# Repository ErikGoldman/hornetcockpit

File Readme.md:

# Stuff to buy

* [Buttons](https://www.aliexpress.us/item/3256807596969239.html?spm=a2g0o.order_list.order_list_main.17.32181802tbzOcq&gatewayAdapt=glo2usa)
  * 3x for landing panel, 1x for emergency jet button

* [Rotary switches](https://www.aliexpress.us/item/3256806749667426.html?gps-id=pcStoreJustForYou&scm=1007.23125.137358.0&scm_id=1007.23125.137358.0&scm-url=1007.23125.137358.0&pvid=9bd218e7-9fd3-4785-a63d-b64e5d39fffa&_t=gps-id%3ApcStoreJustForYou%2Cscm-url%3A1007.23125.137358.0%2Cpvid%3A9bd218e7-9fd3-4785-a63d-b64e5d39fffa%2Ctpp_buckets%3A668%232846%238116%232002&pdp_npi=4%40dis%21USD%211.56%211.56%21%21%2111.33%2111.33%21%402103246617354162549406696e5c9c%2112000038783963415%21rec%21US%212054727994%21X&spm=a2g0o.store_pc_home.smartJustForYou_2004689678069.1005006935982178&gatewayAdapt=glo2usa)
  * 2 x 3-position for the DDI on/day/night
  * 1 x 5-position for jett select on the button box

* [Rtoary encoder](https://www.aliexpress.us/item/3256804721655912.html?spm=a2g0o.order_list.order_list_main.42.32181802tbzOcq&gatewayAdapt=glo2usa)
  * 2 for the UFC comm knobs

* [Switches](https://www.aliexpress.us/item/3256803381777279.html?spm=a2g0o.order_list.order_list_main.53.32181802tbzOcq&gatewayAdapt=glo2usa)
  * 4 x On-Off for the landing panel
  * 1 x On-Off-On for the landing panel (flaps switch)

* [Heavy on/off switch](https://www.aliexpress.us/item/3256807335530736.html?spm=a2g0o.order_list.order_list_main.72.32181802tbzOcq&gatewayAdapt=glo2usa)
  * 1  for Master Arm
  * 1 for landing gear on button box

* [Infinite metric inserts](https://www.aliexpress.us/item/3256806602613585.html?spm=a2g0o.order_list.order_list_main.78.32181802tbzOcq&gatewayAdapt=glo2usa)
  * You'll need M2, M3, and M4. Length doesn't matter that much.

* [Tactile switches](https://www.aliexpress.us/item/3256806726559452.html?spm=a2g0o.order_list.order_list_main.93.32181802tbzOcq&gatewayAdapt=glo2usa)
  * You'll need ~25 B3F-1025 buttons for the UFC

* [LED tactile switches](https://www.aliexpress.us/item/3256805751476152.html?spm=a2g0o.order_list.order_list_main.98.32181802tbzOcq&gatewayAdapt=glo2usa)
  * You'll need 40 for the DDIs. Might as well get green even if we're not lighting them up but up to you.

* [Potentiometers](https://www.aliexpress.us/item/3256806040646290.html?spm=a2g0o.productlist.main.81.187260260QF0hw&algo_pvid=84c07bf7-0fe9-4ebc-8951-d23a6eb7d641&algo_exp_id=84c07bf7-0fe9-4ebc-8951-d23a6eb7d641-40&pdp_npi=4%40dis%21USD%212.18%211.42%21%21%2115.86%2110.31%21%402103209b17354167733238770e9e3c%2112000036367857193%21sea%21US%212054727994%21X&curPageLogUid=bQxrv8cRZnlX&utparam-url=scene%3Asearch%7Cquery_from%3A)
  * 4 total for the DDI brightness and contrast

* [Micro limit switches](https://www.aliexpress.us/item/3256805410237576.html?spm=a2g0o.productlist.main.5.6b0730fa74hx8l&algo_pvid=17648130-baef-43c8-b3cf-31d32c0792a4&algo_exp_id=17648130-baef-43c8-b3cf-31d32c0792a4-2&pdp_npi=4%40dis%21USD%211.10%211.10%21%21%211.10%211.10%21%402103246617354176043596466e5ca7%2112000033693394511%21sea%21US%212054727994%21X&curPageLogUid=lkwrLgLVjWpn&utparam-url=scene%3Asearch%7Cquery_from%3A)
  * 4x for the parking brake

* [Lots of metric screws](https://www.aliexpress.us/item/3256806962079941.html?spm=a2g0o.productlist.main.35.165f4ee7NPA8oA&algo_pvid=deff47b0-62d4-4d0a-a1f7-c938c3e3a578&algo_exp_id=deff47b0-62d4-4d0a-a1f7-c938c3e3a578-17&pdp_npi=4%40dis%21USD%218.67%215.11%21%21%2163.03%2137.19%21%40210313e917354168483187774ed791%2112000039591786388%21sea%21US%212054727994%21X&curPageLogUid=KvpNKoQBOxiE&utparam-url=scene%3Asearch%7Cquery_from%3A)
  * Either buy a few packs or just go to a hardware store and get the ones you need. You'll use M2, M3, and M4 screws for this project.

* [S2 minis](https://www.aliexpress.us/item/3256807363603425.html?spm=a2g0o.productlist.main.1.6cab32c62R9qUC&algo_pvid=e15310bf-956b-4c9a-90cd-317f5ae7b5d6&algo_exp_id=e15310bf-956b-4c9a-90cd-317f5ae7b5d6-0&pdp_npi=4%40dis%21USD%212.69%212.69%21%21%212.69%212.69%21%4021030ea417354171282754704eed54%2112000041255726730%21sea%21US%212054727994%21X&curPageLogUid=sDNxCo08kLpN&utparam-url=scene%3Asearch%7Cquery_from%3A)
  * You'll need 4: 2x DDI, 1x UFC, 1x landing box

* [Jumper Wire](https://www.aliexpress.us/item/3256805315188857.html?spm=a2g0o.productlist.main.1.284553e8uw4adZ&algo_pvid=8f88dacd-bd79-440a-a395-cd9433769ec0&algo_exp_id=8f88dacd-bd79-440a-a395-cd9433769ec0-0&pdp_npi=4%40dis%21USD%211.51%211.51%21%21%211.51%211.51%21%402103205117354174202164517e1dda%2112000033328892981%21sea%21US%212054727994%21X&curPageLogUid=3if8GBiVVzNk&utparam-url=scene%3Asearch%7Cquery_from%3A)
  * Get 2x Female-to-Female and 2x Male-To-Male

* [Flexible wire](https://www.aliexpress.us/item/3256807235268703.html?spm=a2g0o.productlist.main.5.394570bexrCgaY&algo_pvid=9f551878-bcfe-470d-863e-4979d61cdf85&algo_exp_id=9f551878-bcfe-470d-863e-4979d61cdf85-2&pdp_npi=4%40dis%21USD%2112.35%2112.35%21%21%2112.35%2112.35%21%402103245417354175065011181ebf23%2112000040685450213%21sea%21US%212054727994%21X&curPageLogUid=fGUFL1tVhyTT&utparam-url=scene%3Asearch%7Cquery_from%3A)
  * 28 AWG flexible silicone wire is handy here

# Assemble

## Printing

Print one of everything in FilesToPrint. Let me know if you run into any trouble but otherwise just keep it organized since you'll have a lot of parts sitting around.

We'll be replacing all of the imperial inserts and screws with metric ones since metric is way cheaper and easier to source. Take a look at "Assembly instructions" to see how everything fits together and use the similarly-sized metric insert and screw instead of whatever is listed there.

There are backplates for the two DDIs, master arm panel, and UFC. Print those and they should line up next to each other. The desk clamps mount on the DDIs and on the master arm panel and allow you to screw into your desk. You may want to put some foam or something soft in the clamp to prevent scratching on your desk.

## PCBs

NextPCB is crazy cheap. There should be NextPCB-compatible BOMs in the directories and the .zip files should be what PCBNext wants to give a quote and manufacture everything.

Note that the holes in the DDIs are too small for your rotary encoders and potentiometers. I dremeled them to be a bit larger and everything was fine. I could modify the PCB to fit the new components but I'm lazy.

## Electrical

Look at the top of the .ino files to see the pin assignments. Look up how to wire buttons and switches if you haven't done it before, the internet will help here.

## Software

Use the .ino sketches to upload to the ESP32s. Note that if you just upload the sketch normally the ESP32 will have its default product ID/serial number/etc. and so you can't have multiple of them connected to DCS at the same time. To fix that, go to Tools -> USB CDC On Boot and set to "Disabled". They should now have descriptive names like "F18 UFC" in DCS.

At the top of the DDI.ino sketch you should see `#define IS_LEFT_DDI 1` -- that should be 1 for for the left DDI but set it to zero before you upload to the right DDI (`#define IS_LEFT_DDI 0`).

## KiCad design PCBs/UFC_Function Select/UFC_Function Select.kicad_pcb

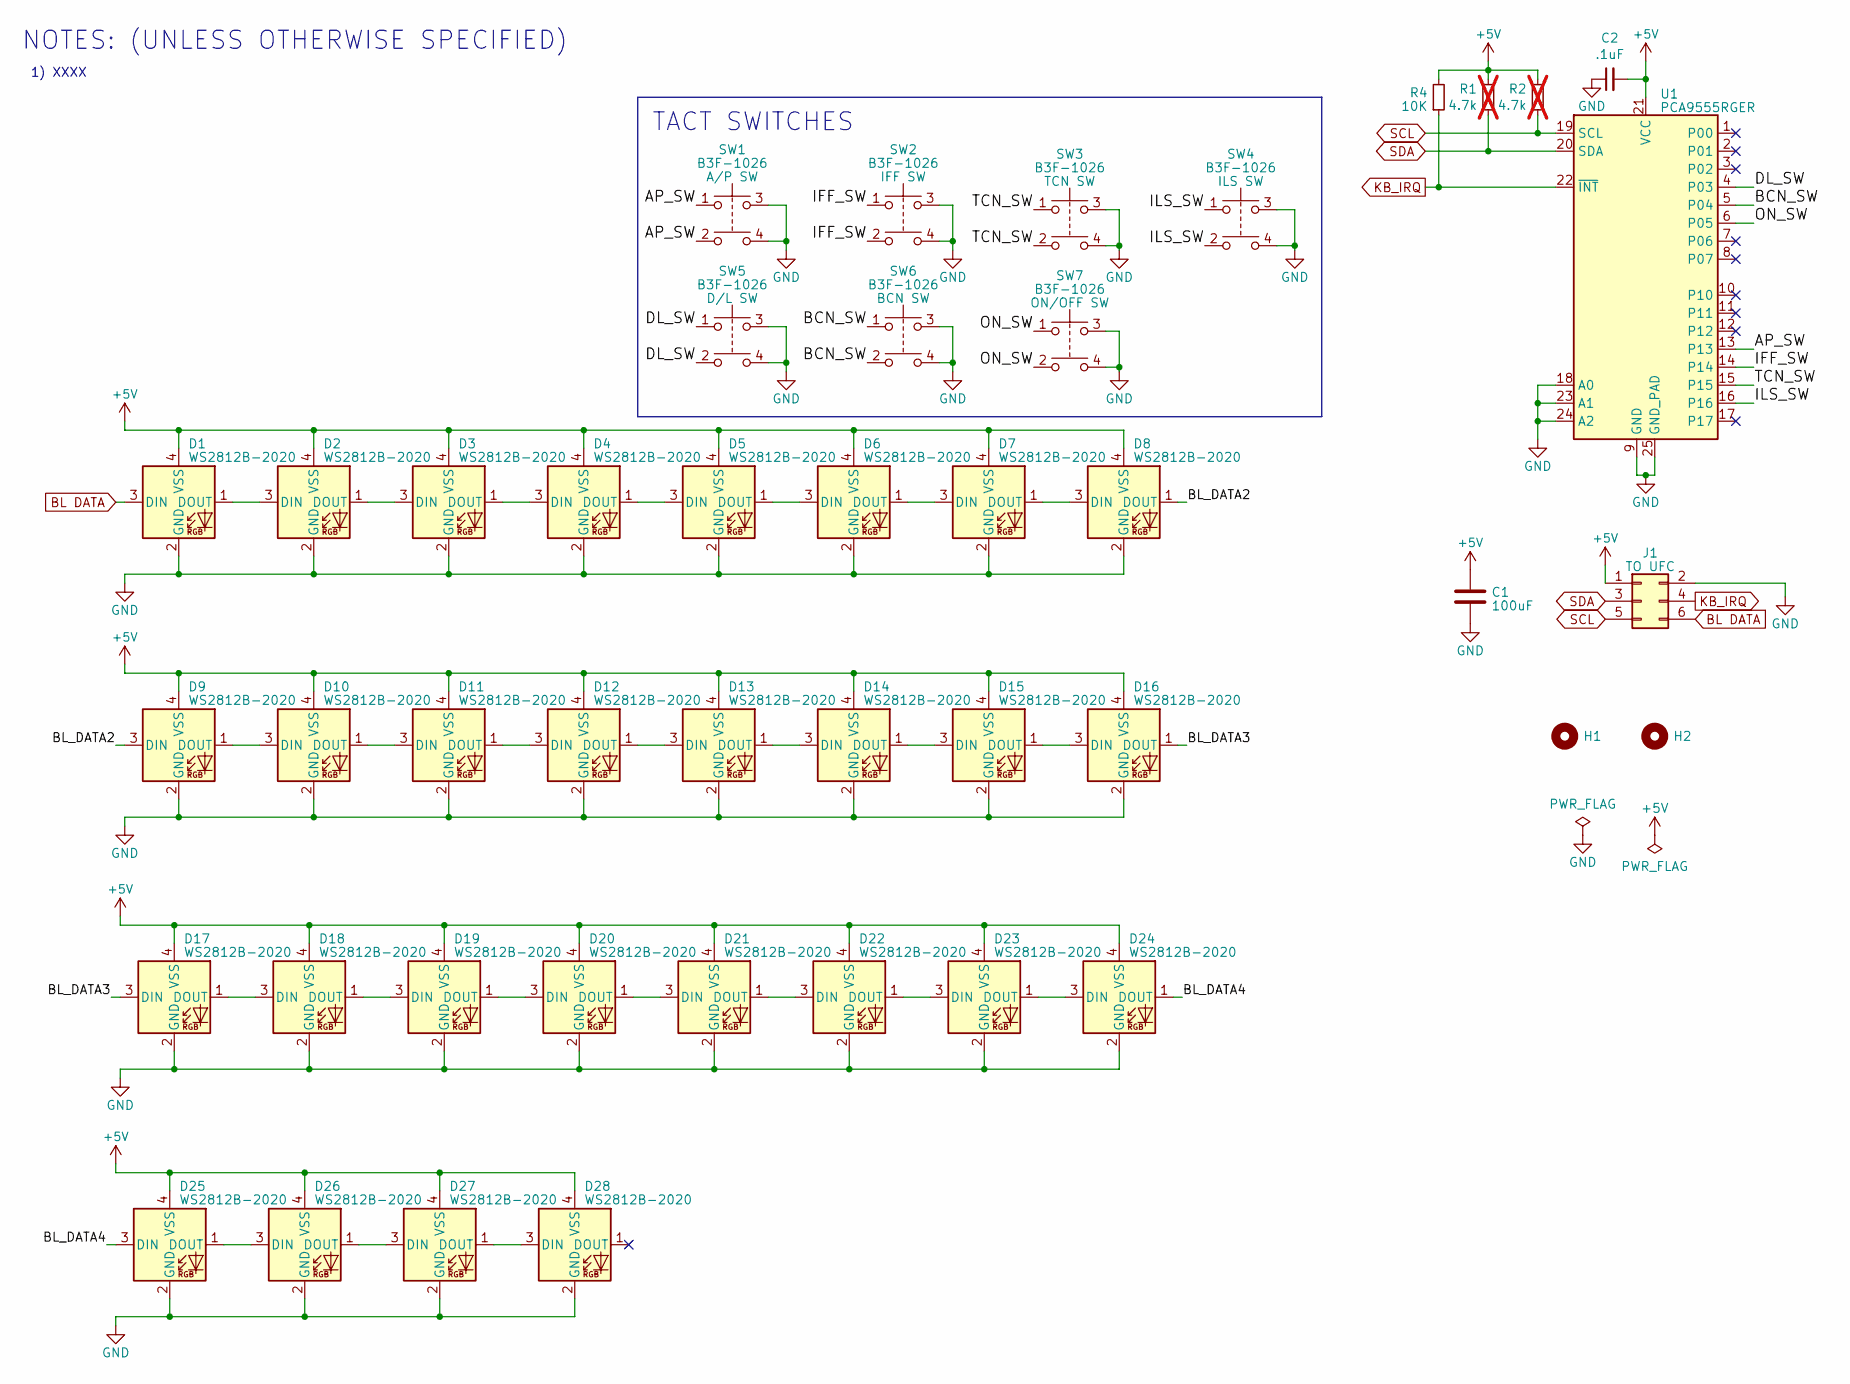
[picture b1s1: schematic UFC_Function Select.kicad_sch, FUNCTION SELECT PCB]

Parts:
C1: 100uF; CP_Elec_6.3x5.4; LCSC C2963046
C2: .1uF; C_0603_1608Metric; LCSC C14663
D1, D2, D3, D4, D5, D6, D7, D8, D9, D10, D11, D12, D13, D14, D15, D16, D17, D18, D19, D20, D21, D22, D23, D24, D25, D26, D27, D28: WS2812B-2020; LED_WS2812B-2020_PLCC4_2.0x2.0mm; Manufacturer PN WS2812B-2020; LCSC C965555
H1, H2: MountingHole_3.2mm_M3_DIN965
J1: TO UFC; PinHeader_2x03_P2.54mm_Vertical
R1, R2: 4.7k; R_0603_1608Metric; LCSC C23162; not fitted
R4: 10K; R_0603_1608Metric; LCSC C25804
SW1, SW2, SW3, SW4, SW5, SW6, SW7: B3F-1026; Omron_B3F-1026
U1: PCA9555RGER; VQFN-24-1EP_4x4mm_P0.5mm_EP2.45x2.45mm; LCSC C2652275

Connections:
+5V: C1.1, C2.2, D1.4 (VSS), D2.4 (VSS), D3.4 (VSS), D4.4 (VSS), D5.4 (VSS), D6.4 (VSS), D7.4 (VSS), D8.4 (VSS), D9.4 (VSS), D10.4 (VSS), D11.4 (VSS), D12.4 (VSS), D13.4 (VSS), D14.4 (VSS), D15.4 (VSS), D16.4 (VSS), D17.4 (VSS), D18.4 (VSS), D19.4 (VSS), D20.4 (VSS), D21.4 (VSS), D22.4 (VSS), D23.4 (VSS), D24.4 (VSS), D25.4 (VSS), D26.4 (VSS), D27.4 (VSS), D28.4 (VSS), J1.1, R1.1, R2.2, R4.2, U1.21 (VCC)
/AP_SW: SW1.1, SW1.2, U1.13
/BCN_SW: SW6.1, SW6.2, U1.5 (P04)
/BL_DATA2: D8.1 (DOUT), D9.3 (DIN)
/BL_DATA3: D16.1 (DOUT), D17.3 (DIN)
/BL_DATA4: D24.1 (DOUT), D25.3 (DIN)
/DL_SW: SW5.1, SW5.2, U1.4 (P03)
/IFF_SW: SW2.1, SW2.2, U1.14
/ILS_SW: SW4.1, SW4.2, U1.16
/ON_SW: SW7.1, SW7.2, U1.6 (P05)
/TCN_SW: SW3.1, SW3.2, U1.15
BL DATA: D1.3 (DIN), J1.6
GND: C1.2, C2.1, D1.2 (GND), D2.2 (GND), D3.2 (GND), D4.2 (GND), D5.2 (GND), D6.2 (GND), D7.2 (GND), D8.2 (GND), D9.2 (GND), D10.2 (GND), D11.2 (GND), D12.2 (GND), D13.2 (GND), D14.2 (GND), D15.2 (GND), D16.2 (GND), D17.2 (GND), D18.2 (GND), D19.2 (GND), D20.2 (GND), D21.2 (GND), D22.2 (GND), D23.2 (GND), D24.2 (GND), D25.2 (GND), D26.2 (GND), D27.2 (GND), D28.2 (GND), J1.2, SW1.3, SW1.4, SW2.3, SW2.4, SW3.3, SW3.4, SW4.3, SW4.4, SW5.3, SW5.4, SW6.3, SW6.4, SW7.3, SW7.4, U1.9 (GND), U1.18 (A0), U1.23 (A1), U1.24 (A2), U1.25 (GND_PAD)
KB_IRQ: J1.4, R4.1, U1.22 (~INT)
unnamed: D1.1 (DOUT), D2.3 (DIN)
unnamed: D2.1 (DOUT), D3.3 (DIN)
unnamed: D3.1 (DOUT), D4.3 (DIN)
unnamed: D4.1 (DOUT), D5.3 (DIN)
unnamed: D5.1 (DOUT), D6.3 (DIN)
unnamed: D6.1 (DOUT), D7.3 (DIN)
unnamed: D7.1 (DOUT), D8.3 (DIN)
unnamed: D9.1 (DOUT), D10.3 (DIN)
unnamed: D10.1 (DOUT), D11.3 (DIN)
unnamed: D11.1 (DOUT), D12.3 (DIN)
unnamed: D12.1 (DOUT), D13.3 (DIN)
unnamed: D13.1 (DOUT), D14.3 (DIN)
unnamed: D14.1 (DOUT), D15.3 (DIN)
unnamed: D15.1 (DOUT), D16.3 (DIN)
unnamed: D17.1 (DOUT), D18.3 (DIN)
unnamed: D18.1 (DOUT), D19.3 (DIN)
unnamed: D19.1 (DOUT), D20.3 (DIN)
unnamed: D20.1 (DOUT), D21.3 (DIN)
unnamed: D21.1 (DOUT), D22.3 (DIN)
unnamed: D22.1 (DOUT), D23.3 (DIN)
unnamed: D23.1 (DOUT), D24.3 (DIN)
unnamed: D25.1 (DOUT), D26.3 (DIN)
unnamed: D26.1 (DOUT), D27.3 (DIN)
unnamed: D27.1 (DOUT), D28.3 (DIN)
SCL: J1.5, R2.1, U1.19 (SCL)
SDA: J1.3, R1.2, U1.20 (SDA)

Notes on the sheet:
TACT SWITCHES
NOTES: (UNLESS OTHERWISE SPECIFIED)
1) XXXX

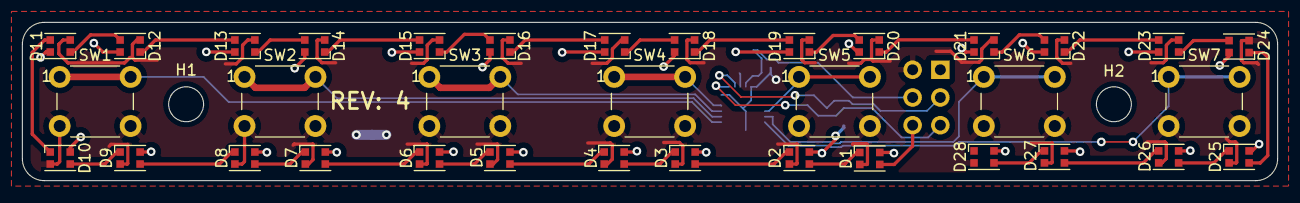
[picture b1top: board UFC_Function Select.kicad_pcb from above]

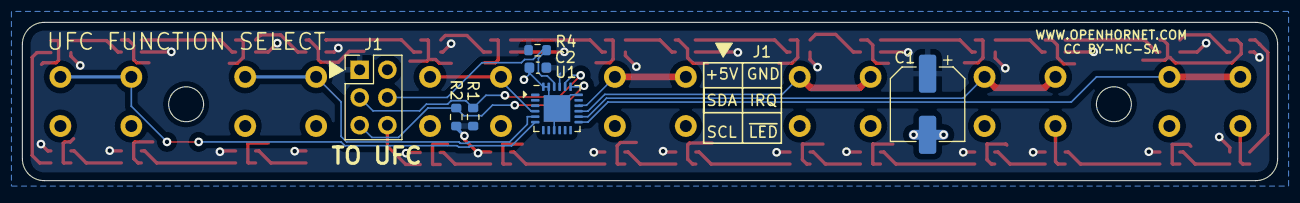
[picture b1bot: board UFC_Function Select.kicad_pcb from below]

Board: 2 copper layers, 115.0 x 14.5 mm, 44 parts (7 on the bottom side), 40 nets.

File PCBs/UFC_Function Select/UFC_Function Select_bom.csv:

"Id";"Designator";"Footprint";"Quantity";"Designation";"Supplier and ref";
1;"D23,D4,D3,D27,D1,D26,D15,D20,D13,D10,D25,D7,D2,D24,D6,D16,D19,D11,D5,D21,D9,D8,D14,D22,D12,D28,D17,D18";"LED_WS2812B-2020_PLCC4_2.0x2.0mm";28;"WS2812B-2020";;;
2;"SW7,SW4,SW3,SW2,SW1,SW6,SW5";"Omron_B3F-1026";7;"B3F-1026";;;
3;"J1";"PinHeader_2x03_P2.54mm_Vertical";1;"TO UFC";;;
4;"U1";"VQFN-24-1EP_4x4mm_P0.5mm_EP2.45x2.45mm";1;"PCA9555RGER";;;
5;"C1";"CP_Elec_6.3x5.4";1;"100uF";;;
6;"C2";"C_0603_1608Metric";1;".1uF";;;
7;"R4";"R_0603_1608Metric";1;"10K";;;

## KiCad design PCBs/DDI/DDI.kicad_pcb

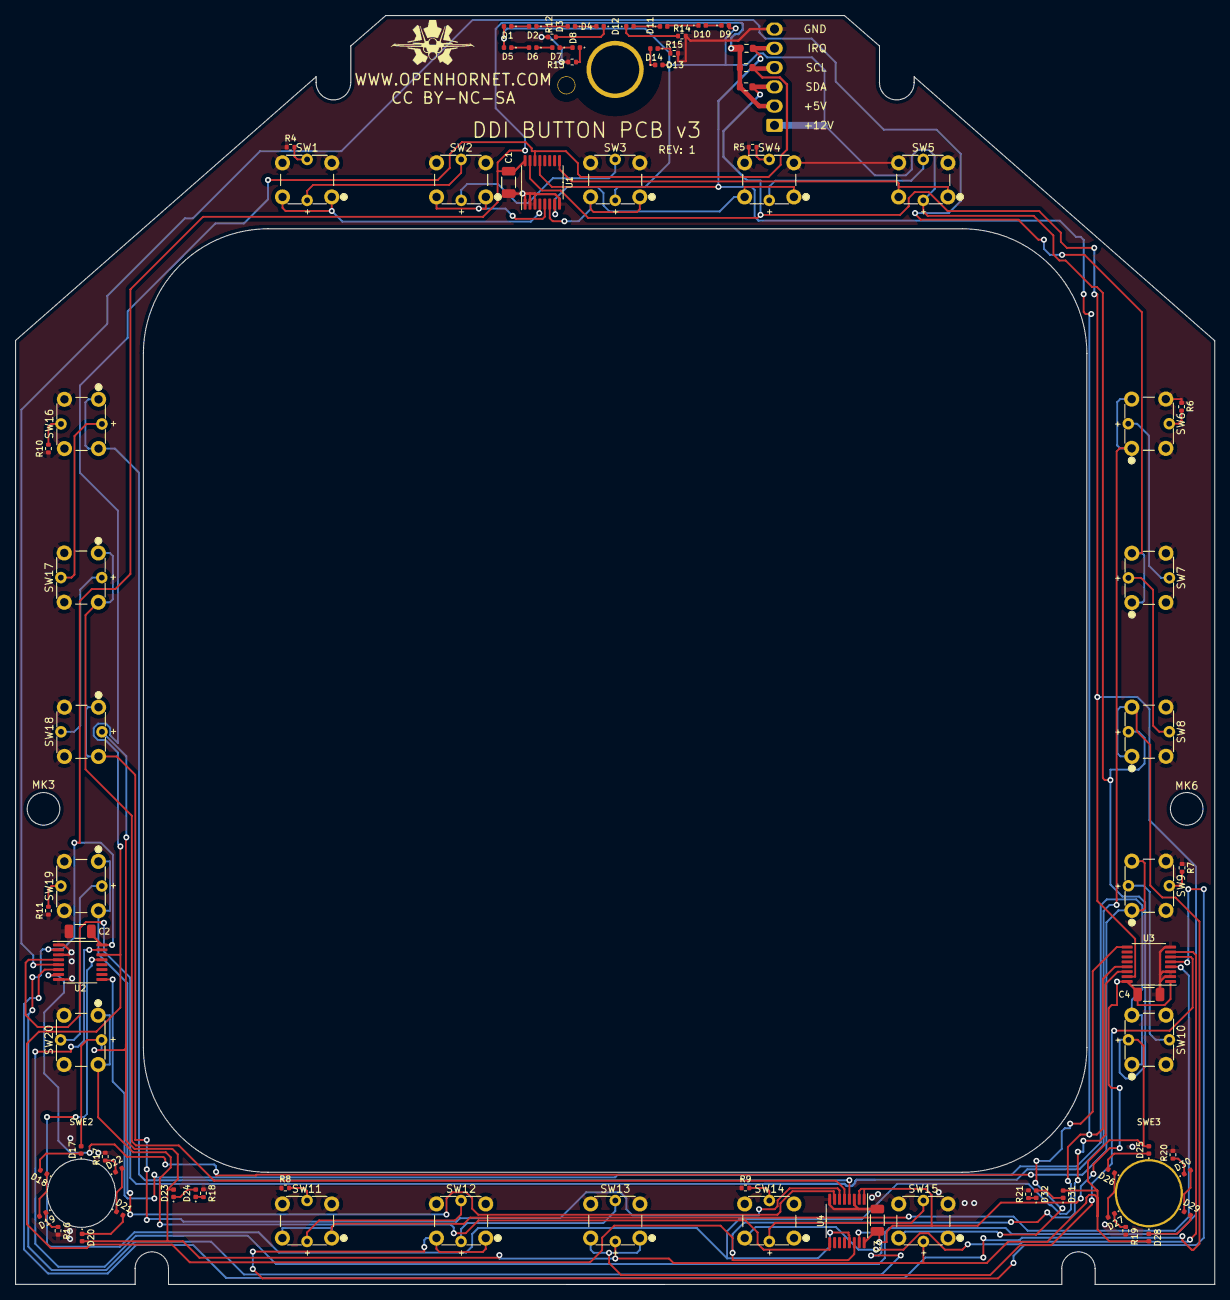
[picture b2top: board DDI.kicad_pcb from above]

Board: 2 copper layers, 158.2 x 167.4 mm, 85 parts (1 on the bottom side), 56 nets.

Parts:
C1, C2, C3, C4: 47uF; C_1206_3216Metric
D1, D2, D3, D4, D5, D6, D7, D8, D9, D10, D11, D12, D13, D14, D17, D18, D19, D20, D21, D22, D23, D24, D25, D26, D27, D28, D29, D30, D31, D32: LED; LED_0402_1005Metric
J1: Conn_01x06; Molex_KK-254_AE-6410-06A_1x06_P2.54mm_Vertical
MK3, MK6: MH; MountingHole_4.3mm_M4
R1, R2, R3: 10K; R_0603_1608Metric
R4, R6, R8, R10, R16, R17, R19, R20: 150; R_0402_1005Metric
R5, R7, R9, R11, R15, R18, R21: 270; R_0402_1005Metric
R12, R13, R14: 33; R_0402_1005Metric
SW1, SW2, SW3, SW4, SW5, SW6, SW7, SW8, SW9, SW10, SW11, SW12, SW13, SW14, SW15, SW16, SW17, SW18, SW19, SW20: TL1240GQ
SWE1: MRY106_RotarySW
SWE2, SWE3: MountingHole_8.4mm_M8
U1, U2, U3, U4: TCA9554PWR; TSSOP-16_4.4x5mm_P0.65mm

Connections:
+5V: C1.1, C2.1, C3.1, C4.1, J1.2, R1.1, R2.1, R3.1, U1.16, U2.2, U2.16, U3.1, U3.16, U4.1, U4.2, U4.16
/U1P0: SW1.1, U1.4
/U1P1: SW2.1, U1.5
/U1P2: SW3.1, U1.6
/U1P3: SW4.1, U1.7
/U1P4: SW5.1, U1.9
/U2P0: SW6.1, U2.4
/U2P1: SW7.1, U2.5
/U2P2: SW8.1, U2.6
/U2P3: SW9.1, U2.7
/U2P4: SW10.1, U2.9
/U3P0: SW11.1, U3.4
/U3P1: SW12.1, U3.5
/U3P2: SW13.1, U3.6
/U3P3: SW14.1, U3.7
/U3P4: SW15.1, U3.9
/U4P0: SW16.1, U4.4
/U4P1: SW17.1, U4.5
/U4P2: SW18.1, U4.6
/U4P3: SW19.1, U4.7
/U4P4: SW20.1, U4.9
GND: C1.2, C2.2, C3.2, C4.2, J1.6, R4.1, R5.1, R6.1, R7.1, R8.1, R9.1, R10.1, R11.1, R12.2, R13.2, R14.2, R15.2, R16.2, R17.2, R18.2, R19.2, R20.2, R21.2, SW1.2, SW2.2, SW3.2, SW4.2, SW5.2, SW6.2, SW7.2, SW8.2, SW9.2, SW10.2, SW11.2, SW12.2, SW13.2, SW14.2, SW15.2, SW16.2, SW17.2, SW18.2, SW19.2, SW20.2, U1.1, U1.2, U1.3, U1.8, U2.1, U2.3, U2.8, U3.2, U3.3, U3.8, U4.3, U4.8
IRQ: J1.5, R1.2, U1.13, U2.13, U3.13, U4.13
unnamed: D1.1, D2.2
unnamed: D2.1, D3.2
unnamed: D3.1, D4.2
unnamed: D4.1, R12.1
unnamed: D5.1, D6.2
unnamed: D6.1, D7.2
unnamed: D7.1, D8.2
unnamed: D8.1, R13.1
unnamed: D10.1, D11.2
unnamed: D9.1, D10.2
unnamed: D11.1, D12.2
unnamed: D12.1, R14.1
unnamed: D13.1, D14.2
unnamed: D14.1, R15.1
unnamed: D17.1, D18.2
unnamed: D18.1, D19.2
unnamed: D19.1, R16.1
unnamed: D20.1, D21.2
unnamed: D21.1, D22.2
unnamed: D22.1, R17.1
unnamed: D23.1, D24.2
unnamed: D24.1, R18.1
unnamed: D25.1, D26.2
unnamed: D26.1, D27.2
unnamed: D27.1, R19.1
unnamed: D28.1, D29.2
unnamed: D29.1, D30.2
unnamed: D30.1, R20.1
unnamed: D31.1, D32.2
unnamed: D32.1, R21.1
SCL: J1.4, R2.2, U1.14, U2.14, U3.14, U4.14
SDA: J1.3, R3.2, U1.15, U2.15, U3.15, U4.15
VCC: D1.2, D5.2, D9.2, D13.2, D17.2, D20.2, D23.2, D25.2, D28.2, D31.2, J1.1

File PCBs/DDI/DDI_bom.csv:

"Id";"Designator";"Footprint";"Quantity";"Designation";"Supplier and ref";
1;"C1,C2,C3,C4";"C_1206_3216Metric";4;"47uF";;;
2;"D1,D2,D3,D4,D5,D6,D7,D8,D9,D10,D11,D12,D13,D14,D17,D18,D19,D20,D21,D22,D23,D24,D25,D26,D27,D28,D29,D30,D31,D32";"LED_0402_1005Metric";30;"LED";;;
3;"R1,R2,R3";"R_0603_1608Metric";3;"10K";;;
4;"R4,R6,R8,R10,R16,R17,R19,R20";"R_0402_1005Metric";8;"150";;;
5;"R5,R9,R11,R15,R18,R21,R7";"R_0402_1005Metric";7;"270";;;
6;"R12,R13,R14";"R_0402_1005Metric";3;"33";;;
7;"U1,U2,U3,U4";"TSSOP-16_4.4x5mm_P0.65mm";4;"TCA9554PWR";;;
8;"SW1,SW3,SW4,SW5,SW6,SW7,SW8,SW9,SW10,SW11,SW12,SW13,SW14,SW15,SW16,SW17,SW18,SW20,SW2,SW19";"TL1240GQ";20;"TL1240GQ";;;
9;"G***,G***";"OH_LOGO_ONLY_11x6mm";2;"OH_LOGO_ONLY_11x6mm";;;

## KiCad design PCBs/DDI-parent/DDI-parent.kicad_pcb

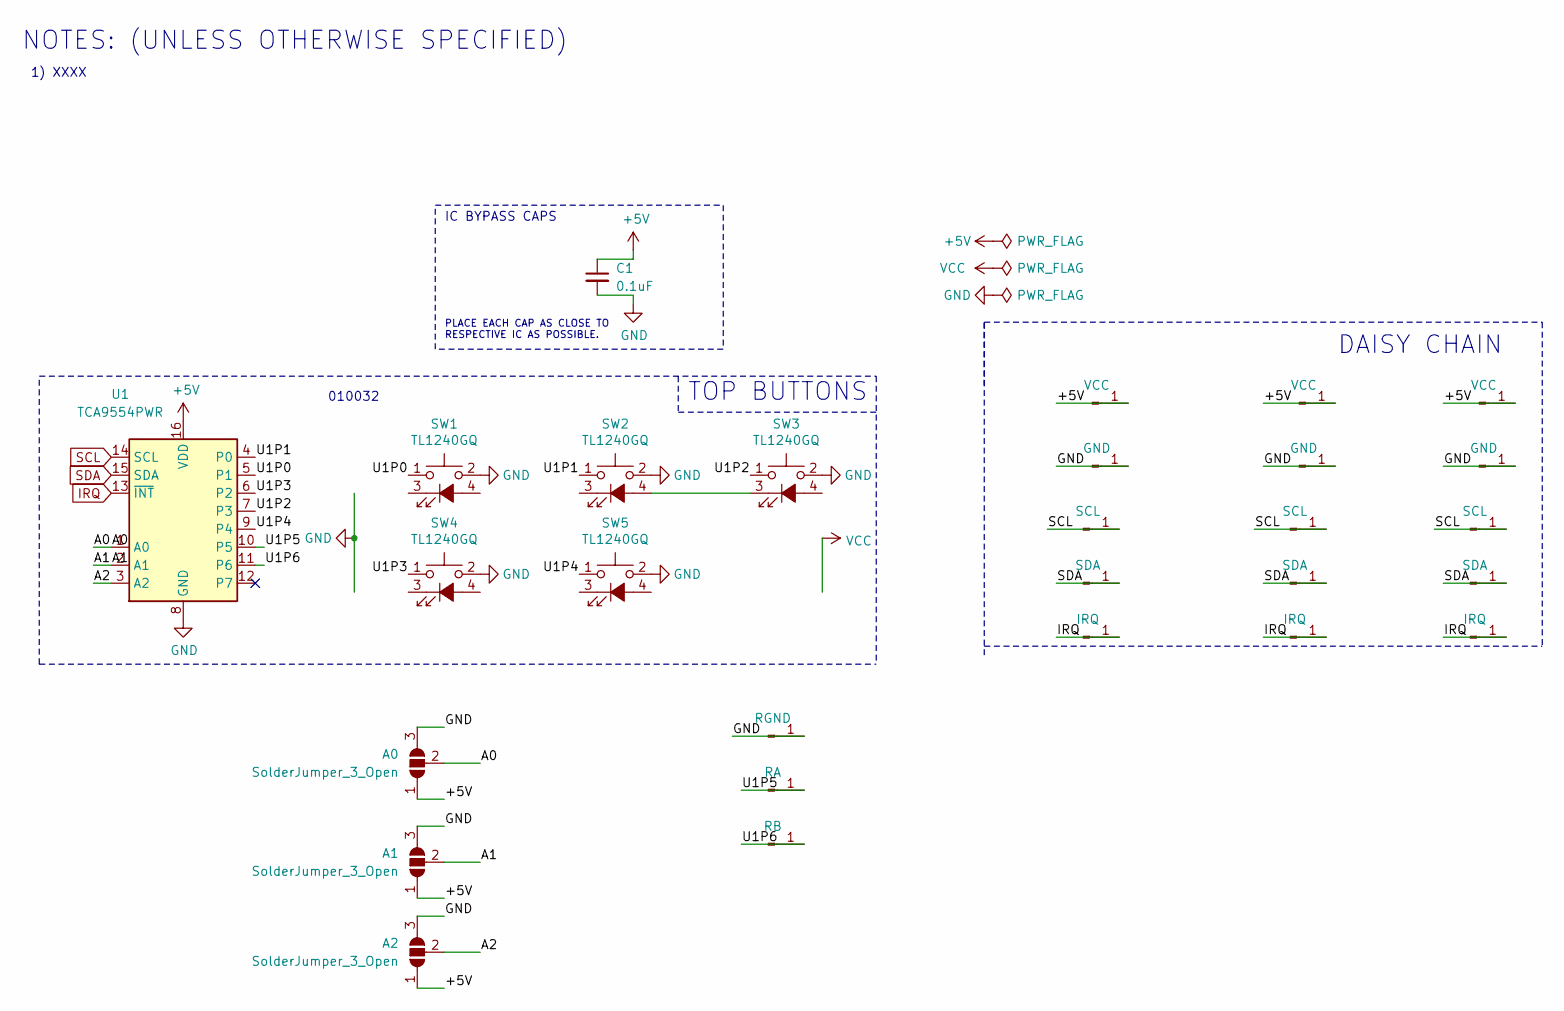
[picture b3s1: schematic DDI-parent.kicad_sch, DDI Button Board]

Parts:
A0, A1, A2: SolderJumper_3_Open; SolderJumper-3_P1.3mm_BothDisconnected_RoundedPad1.0x1.5mm
C1: 0.1uF; C_0402_1005Metric; LCSC C96123
J1, J9, J14: VCC; SolderWirePad_1x01_SMD_4x3mm
J2, J10, J15: GND; SolderWirePad_1x01_SMD_4x3mm
J3, J6, J11: SCL; SolderWirePad_1x01_SMD_4x3mm
J4, J7, J12: SDA; SolderWirePad_1x01_SMD_4x3mm
J5, J8, J13: IRQ; SolderWirePad_1x01_SMD_4x3mm
J16: RGND; SolderWirePad_1x01_SMD_4x3mm
J17: RA; SolderWirePad_1x01_SMD_4x3mm
J18: RB; SolderWirePad_1x01_SMD_4x3mm
SW1, SW2, SW3, SW4, SW5: TL1240GQ
U1: TCA9554PWR; TSSOP-16_4.4x5mm_P0.65mm; LCSC C477924

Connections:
+5V: A0.1 (A), A1.1 (A), A2.1 (A), C1.1, J1.1, J9.1, J14.1, U1.16 (VDD)
/A0: A0.2 (C), U1.1 (A0)
/A1: A1.2 (C), U1.2 (A1)
/A2: A2.2 (C), U1.3 (A2)
/U1P0: SW1.1, U1.5 (P1)
/U1P1: SW2.1, U1.4 (P0)
/U1P2: SW3.1, U1.7 (P3)
/U1P3: SW4.1, U1.6 (P2)
/U1P4: SW5.1, U1.9 (P4)
/U1P5: J17.1, U1.10 (P5)
/U1P6: J18.1, U1.11 (P6)
GND: A0.3 (B), A1.3 (B), A2.3 (B), C1.2, J2.1, J10.1, J15.1, J16.1, SW1.2, SW2.2, SW3.2, SW4.2, SW5.2, U1.8 (GND)
IRQ: J5.1, J8.1, J13.1, U1.13 (~INT)
SCL: J3.1, J6.1, J11.1, U1.14 (SCL)
SDA: J4.1, J7.1, J12.1, U1.15 (SDA)

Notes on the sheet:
010032
1) XXXX
DAISY CHAIN
NOTES: (UNLESS OTHERWISE SPECIFIED)
TOP BUTTONS
PLACE EACH CAP AS CLOSE TO RESPECTIVE IC AS POSSIBLE.
IC BYPASS CAPS

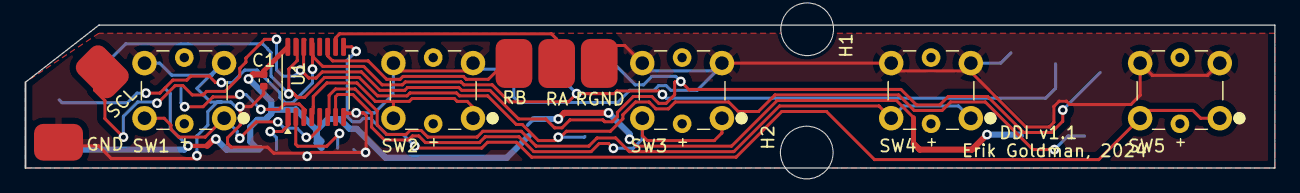
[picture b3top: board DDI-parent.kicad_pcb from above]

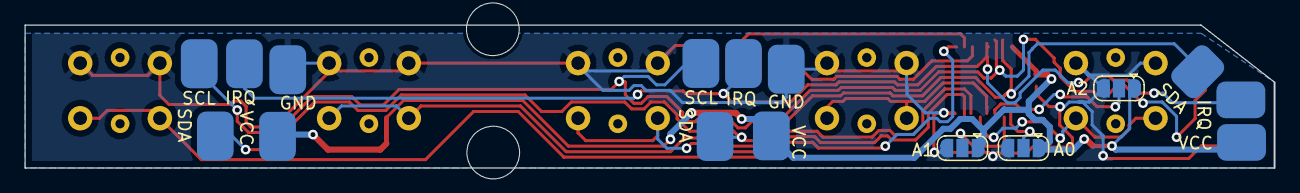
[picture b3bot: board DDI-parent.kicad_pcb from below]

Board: 2 copper layers, 102.0 x 11.7 mm, 30 parts (16 on the bottom side), 15 nets.

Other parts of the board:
H1, H2: MH; MountingHole_4.3mm_M4

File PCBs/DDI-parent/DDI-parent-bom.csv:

"S/N";"Designator";"Quantity";"Manufacturer Part Number";"Procurement Type";"Customer Note"
1;"U1";1;"TCA9554PWR";"--";"--"
2;"C1";1;"CL05B104KP5NNNC";"0.1uF";;;

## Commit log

2024-11-21 new stuff
2024-11-22 shipped off v1.1
2024-12-28 stash
2024-12-28 complete for now

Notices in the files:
PCBs/DDI-parent/DDI-parent.kicad_sch:
CC BY-NC-SA
